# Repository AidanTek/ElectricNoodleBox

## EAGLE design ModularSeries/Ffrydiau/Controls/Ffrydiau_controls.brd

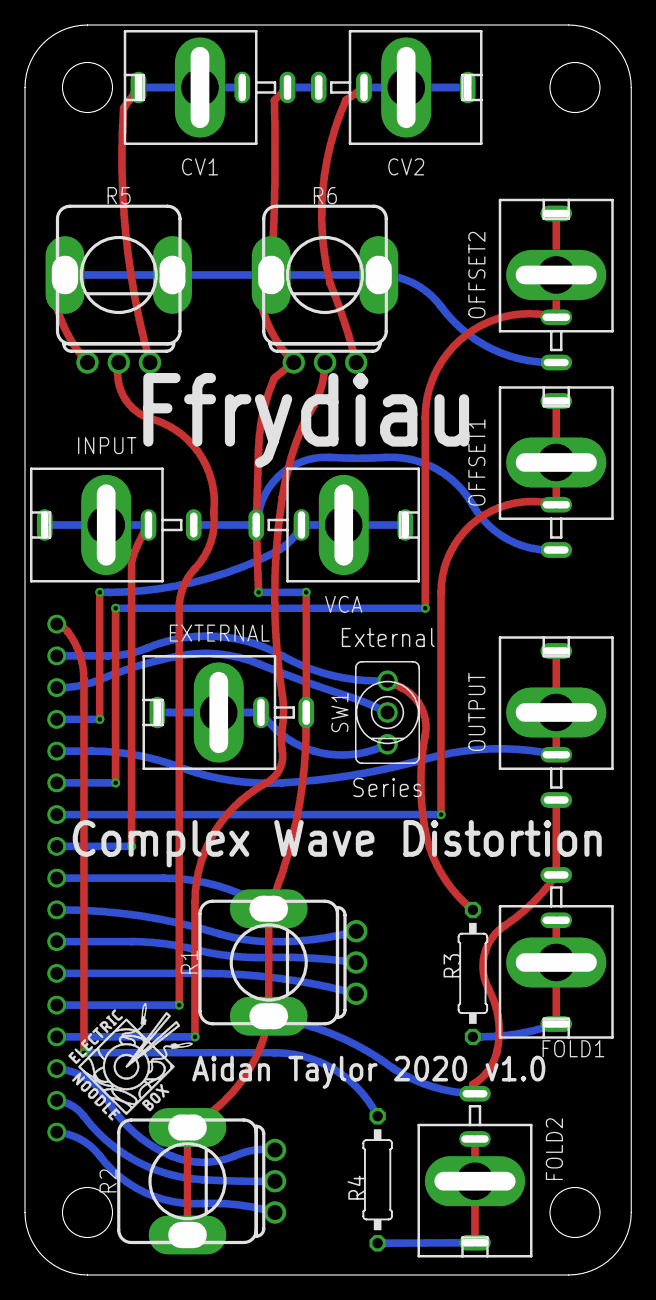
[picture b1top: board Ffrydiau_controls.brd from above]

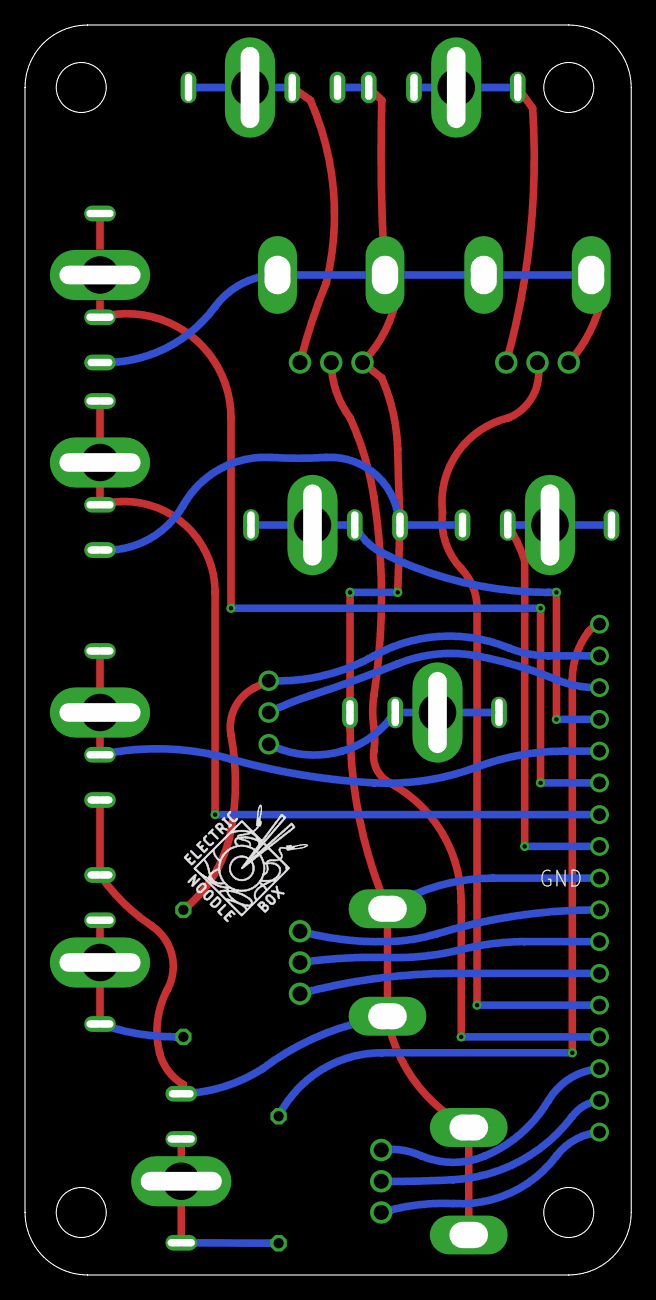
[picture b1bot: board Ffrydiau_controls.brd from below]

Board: 2 copper layers, 48.5 x 100.0 mm, 20 parts (2 on the bottom side), 22 nets.

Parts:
BOARD1: FFRYDIAU_LINK; FFRYDIAU
CV1, CV2: COMBI-JACKCINCHNANA; NEWCOMBOJACK_PANEL
EXTERNAL: COMBI-JACKCINCHNANA; NEWCOMBOJACK_PANEL
FOLD1, FOLD2: COMBI-JACKCINCHNANA; NEWCOMBOJACK_PANEL
INPUT: COMBI-JACKCINCHNANA; NEWCOMBOJACK_PANEL
OFFSET1, OFFSET2: COMBI-JACKCINCHNANA; NEWCOMBOJACK_PANEL
OUTPUT: COMBI-JACKCINCHNANA; NEWCOMBOJACK_PANEL
R1, R2, R5, R6: B100K; ALPHA_RV09_9MMPOT
R3, R4: 100Ω; 0207/10
SW1: SPDT_SWITCHDW1; MICRODPDT-DW1
U$1, U$2: LOGO10X10
VCA: COMBI-JACKCINCHNANA; NEWCOMBOJACK_PANEL

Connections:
AGND: BOARD1.GND, CV1.S, CV2.S, EXTERNAL.S, FOLD1.S, FOLD2.S, INPUT.S, OFFSET1.S, OFFSET2.S, OUTPUT.S, R1.LUGL, R1.LUGR, R2.LUGL, R2.LUGR, R5.C1, R5.LUGL, R5.LUGR, R6.C1, R6.LUGL, R6.LUGR, VCA.S
unnamed: CV1.CONN, CV1.T1, CV1.T2, R5.C3
unnamed: BOARD1.CV1, R5.C2
unnamed: BOARD1.SIG, INPUT.CONN, INPUT.T1, INPUT.T2
unnamed: BOARD1.OUT, OUTPUT.CONN, OUTPUT.T1, OUTPUT.T2
unnamed: BOARD1.POT1_2, R1.C2
unnamed: BOARD1.OFS1, OFFSET1.CONN, OFFSET1.T1, OFFSET1.T2
unnamed: BOARD1.OFS2, OFFSET2.CONN, OFFSET2.T1, OFFSET2.T2
unnamed: BOARD1.VCA, VCA.CONN, VCA.T1, VCA.T2
unnamed: BOARD1.POT1_1, R1.C1
unnamed: BOARD1.POT1_3, R1.C3
unnamed: BOARD1.POT2_2, R2.C2
unnamed: BOARD1.POT2_3, R2.C3
unnamed: BOARD1.POT2_1, R2.C1
unnamed: BOARD1.SWITCH_S, R3.1, SW1.C1
unnamed: FOLD1.CONN, FOLD1.T1, FOLD1.T2, R3.2
unnamed: BOARD1.SWITCH_R, SW1.C2
unnamed: EXTERNAL.CONN, EXTERNAL.T1, EXTERNAL.T2, SW1.C3
unnamed: BOARD1.FOLD2, R4.1
unnamed: FOLD2.CONN, FOLD2.T1, FOLD2.T2, R4.2
unnamed: CV2.CONN, CV2.T1, CV2.T2, R6.C3
unnamed: BOARD1.CV2, R6.C2

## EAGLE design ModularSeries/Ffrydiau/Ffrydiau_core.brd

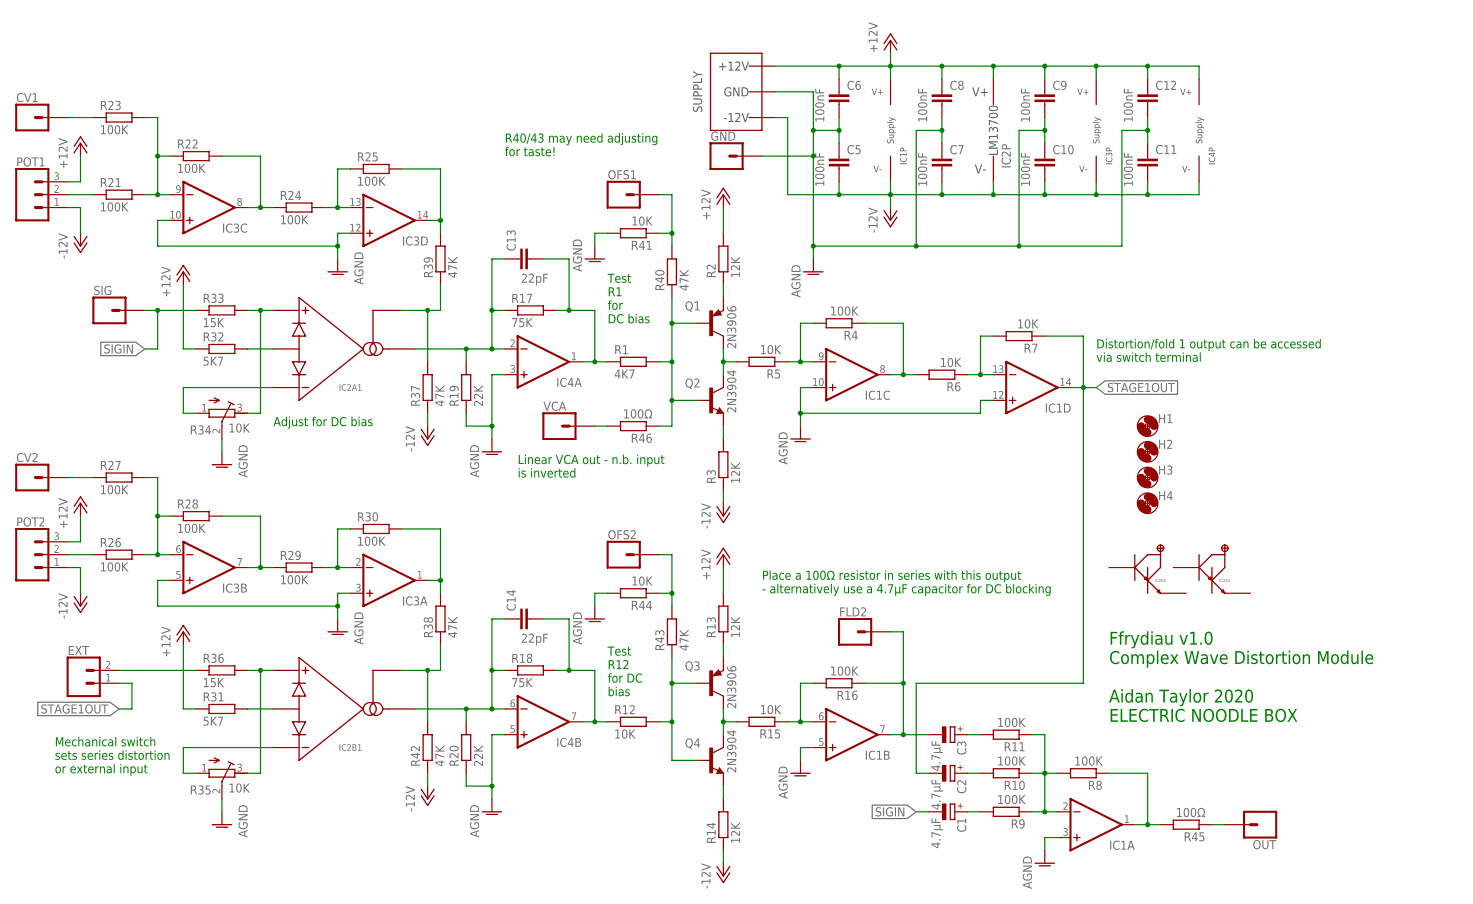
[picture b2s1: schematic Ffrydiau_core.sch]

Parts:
C1, C2, C3: 4.7µF; E2,5-6E
C5, C6, C7, C8, C9, C10, C11, C12: 100nF; C050-025X075
C13, C14: 22pF; C050-025X075
CV1, CV2: 1XWIREPAD; 1X01
EXT: 2XWIREPAD; 1X02
FLD2: 1XWIREPAD; 1X01
GND: 1XWIREPAD; 1X01
H1, H2, H3, H4: MOUNT-HOLE3.2; 3,2
IC1, IC3: TL0X4DIL; DIL14
IC2: LM13700DIL; DIL16
IC4: TL0X2DIL; DIL08
OFS1, OFS2: 1XWIREPAD; 1X01
OUT: 1XWIREPAD; 1X01
POT1, POT2: 3XWIREPAD; 1X03
Q1, Q3: 2N3906; TO92
Q2, Q4: 2N3904; TO92
R1: 4K7; 0207/10
R2, R3, R13, R14: 12K; 0207/10
R4, R8, R9, R10, R11, R16, R21, R22, R23, R24, R25, R26, R27, R28, R29, R30: 100K; 0207/10
R5, R6, R7, R12, R15, R41, R44: 10K; 0207/10
R17, R18: 75K; 0207/10
R19, R20: 22K; 0207/10
R31, R32: 5K7; 0207/10
R33, R36: 15K; 0207/10
R34, R35: 10K; RTRIM3296W
R37, R38, R39, R40, R42, R43: 47K; 0207/10
R45, R46: 100Ω; 0207/10
SIG: 1XWIREPAD; 1X01
VCA: 1XWIREPAD; 1X01
WP1: COMBO_SUPPLY_HEADER; COMBINED_POWER

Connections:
+12V: C6.1, C8.1, C9.1, C12.1, IC1.4 (V+), IC2.11 (V+), IC3.4 (V+), IC4.8 (V+), POT1.3, POT2.3, R2.2, R13.2, R31.1, R32.1, WP1.V+1 (V++), WP1.V+2 (V++), WP1.V+3 (V++)
-12V: C5.2, C7.2, C10.2, C11.2, IC1.11 (V-), IC2.6 (V-), IC3.11 (V-), IC4.4 (V-), POT1.1, POT2.1, R3.1, R14.1, R37.1, R42.1, WP1.V-1 (V--), WP1.V-2 (V--), WP1.V-3 (V--)
AGND: C5.1, C6.2, C7.1, C8.2, C9.2, C10.1, C11.1, C12.2, GND.1, IC1.3 (+IN), IC1.5 (+IN), IC1.10 (+IN), IC1.12 (+IN), IC3.3 (+IN), IC3.5 (+IN), IC3.10 (+IN), IC3.12 (+IN), IC4.3 (+IN), IC4.5 (+IN), R19.1, R20.1, R34.2 (S), R35.2 (S), R41.2, R44.2, WP1.GND1 (AGND), WP1.GND2 (AGND), WP1.GND3 (AGND), WP1.GND4 (AGND), WP1.GND5 (AGND), WP1.GND6 (AGND), WP1.GND7 (AGND), WP1.GND8 (AGND)
unnamed: Q1.2 (B), Q2.2 (B), R1.2, R40.1, R46.1
unnamed: Q1.3 (E), R2.1
unnamed: Q2.3 (E), R3.2
unnamed: Q1.1 (C), Q2.1 (C), R5.2
unnamed: IC1.9 (-IN), R4.2, R5.1
unnamed: IC1.8 (OUT), R4.1, R6.2
unnamed: IC1.13 (-IN), R6.1, R7.2
unnamed: OUT.1, R45.1
unnamed: C13.2, IC4.1 (OUT), R1.1, R17.2
unnamed: C3.+, R11.2
unnamed: C2.+, R10.2
unnamed: C1.+, R9.2
unnamed: IC1.2 (-IN), R8.2, R9.1, R10.1, R11.1
unnamed: IC1.1 (OUT), R8.1, R45.2
unnamed: Q3.2 (B), Q4.2 (B), R12.2, R43.1
unnamed: Q3.3 (E), R13.1
unnamed: Q4.3 (E), R14.2
unnamed: Q3.1 (C), Q4.1 (C), R15.2
unnamed: IC1.6 (-IN), R15.1, R16.2
unnamed: C3.-, FLD2.1, IC1.7 (OUT), R16.1
unnamed: C14.1, IC2.12 (AMPOUT), IC4.6 (-IN), R18.1, R20.2
unnamed: C13.1, IC2.5 (AMPOUT), IC4.2 (-IN), R17.1, R19.2
unnamed: C14.2, IC4.7 (OUT), R12.1, R18.2
unnamed: IC3.9 (-IN), R21.2, R22.1, R23.2
unnamed: IC3.8 (OUT), R22.2, R24.1
unnamed: IC3.13 (-IN), R24.2, R25.1
unnamed: IC3.14 (OUT), R25.2, R39.2
unnamed: CV2.1, R27.1
unnamed: IC3.1 (OUT), R30.2, R38.2
unnamed: POT1.2, R21.1
unnamed: IC3.2 (-IN), R29.2, R30.1
unnamed: CV1.1, R23.1
unnamed: IC3.7 (OUT), R28.2, R29.1
unnamed: IC3.6 (-IN), R26.2, R27.2, R28.1
unnamed: IC2.14 (AMP+), R35.3 (E), R36.2
unnamed: IC2.13 (AMP-), R35.1 (A)
unnamed: IC2.15 (DIODES), R31.2
unnamed: IC2.2 (DIODES), R32.2
unnamed: IC2.1 (AMPBIAS), R37.2, R39.1
unnamed: POT2.2, R26.1
unnamed: IC2.3 (AMP+), R33.2, R34.3 (E)
unnamed: IC2.4 (AMP-), R34.1 (A)
unnamed: IC2.16 (AMPBIAS), R38.1, R42.2
unnamed: OFS1.1, R40.2, R41.1
unnamed: OFS2.1, R43.2, R44.1
unnamed: R46.2, VCA.1
unnamed: EXT.2, R36.1
SIGIN: C1.-, R33.1, SIG.1
STAGE1OUT: C2.-, EXT.1, IC1.14 (OUT), R7.1

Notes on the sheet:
Place a 100Ω resistor in series with this output - alternatively use a 4.7µF capacitor for DC blocking
Distortion/fold 1 output can be accessed via switch terminal
R40/43 may need adjusting for taste!
Linear VCA out - n.b. input is inverted
Adjust for DC bias
Test R1 for DC bias
Test R12 for DC bias
Mechanical switch sets series distortion or external input
Ffrydiau v1.0 Complex Wave Distortion Module Aidan Taylor 2020 ELECTRIC NOODLE BOX

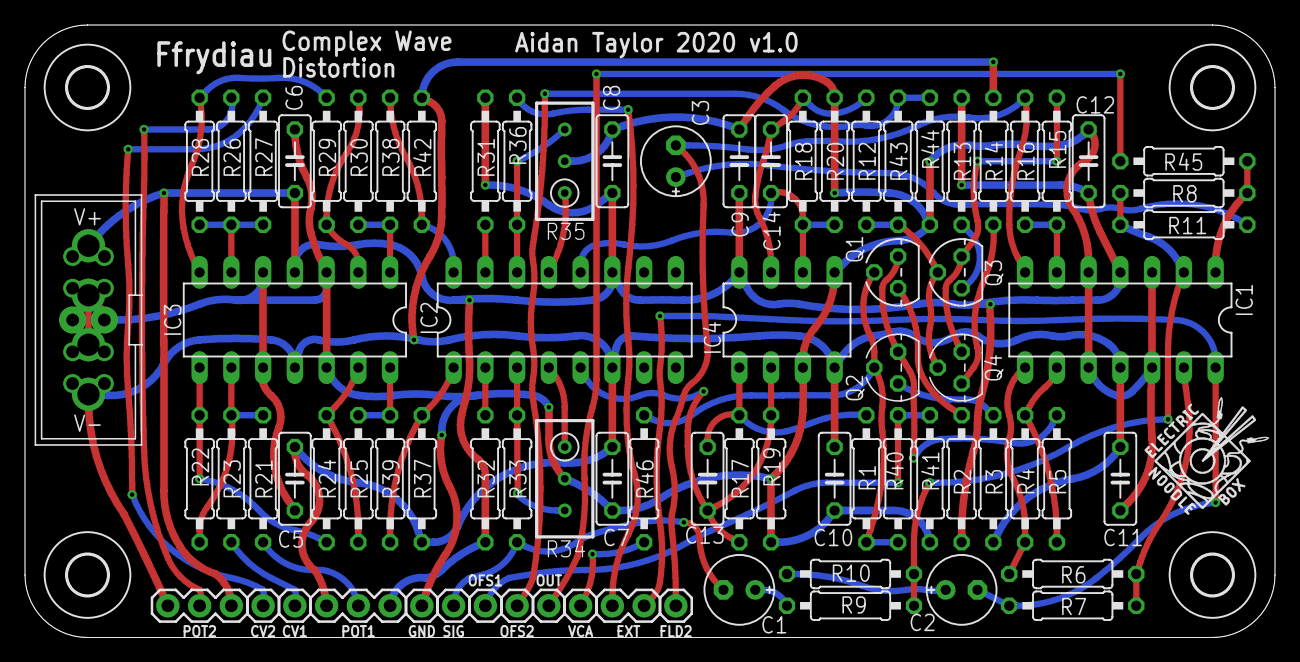
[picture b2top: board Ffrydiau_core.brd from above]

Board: 2 copper layers, 100.0 x 49.0 mm, 85 parts (0 on the bottom side), 52 nets.

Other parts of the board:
U$1: LOGO10X10

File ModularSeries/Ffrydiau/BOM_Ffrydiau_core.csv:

Qty,Value,Package,Parts,Description,RETAILER,CATALOGUE
,,,,,,
16,100K,0207/10,"R4, R8, R9, R10, R11, R16, R21, R22, R23, R24, R25, R26, R27, R28, R29, R30",RESISTOR 1/4W,Farnell,2329853
2,100Ω,0207/10,"R45, R46",RESISTOR 1/4W,Farnell,2329854
7,10K,0207/10,"R5, R6, R7, R12, R15, R41, R44",RESISTOR 1/4W,Farnell,2329855
4,12K,0207/10,"R2, R3, R13, R14",RESISTOR 1/4W,Farnell,2329863
2,15K,0207/10,"R33, R36",RESISTOR 1/4W,Farnell,1563095
2,22K,0207/10,"R19, R20",RESISTOR 1/4W,Farnell,2329901
6,47K,0207/10,"R37, R38, R39, R40, R42, R43",RESISTOR 1/4W,Farnell,2329944
1,4K7,0207/10,R1,RESISTOR 1/4W,Farnell,2329945
2,5K6,0207/10,"R31, R32",RESISTOR 1/4W,Farnell,2329958
2,75K,0207/10,"R17, R18",RESISTOR 1/4W,Farnell,2329972
2,10K,RTRIM3296W,"R34, R35",Trimm resistor 3296W,Farnell,9353186
,,,,,,
2,22pF,C050-025X075,"C13, C14",CAPACITOR Ceramic,Farnell,1457695
8,100nF,C050-025X075,"C5, C6, C7, C8, C9, C10, C11, C12",CAPACITOR Ceramic,Farnell,2797801
3,4.7¬µF,"E2,5-6E","C1, C2, C3","POLARIZED CAPACITOR, Electrolytic 25V+",Farnell,9451234
,,,,,,
2,2N3904,TO92,"Q2, Q4",NPN Transistor TO-92,Farnell,1574370
2,2N3906,TO92,"Q1, Q3",PNP Transistor TO-92,Farnell,1574372
1,LM13700,DIL16,IC2,Dual Transconductance Amplifier with Darlington Buffer,Farnell,3118206
1,TL082,DIL08,IC4,Dual Operational Amplifier,Farnell,1103189
2,TL084,DIL14,"IC1, IC3",Quad Operational Amplifier,Farnell,3005140
,,,,,,
1,Power Header,Power Header,WP1,10 way Shrouded IDC,Farnell,2843527
,,,,,,
9,Jack / Banana Connector,1X01,"CV1, CV2, FLD2, OFS1, OFS2, OUT, SIG, VCA",Banana or Jack patch point (panel part),Farnell,1698951
1,SPDT Mechanical Switch,1X02,EXT,Toggle switch SPDT (panel part),Farnell,9473491
2,B100K Potentiometer,1X03,"POT1, POT2",Taiwan Alpha 16mm (panel part),Rapid,65-0756

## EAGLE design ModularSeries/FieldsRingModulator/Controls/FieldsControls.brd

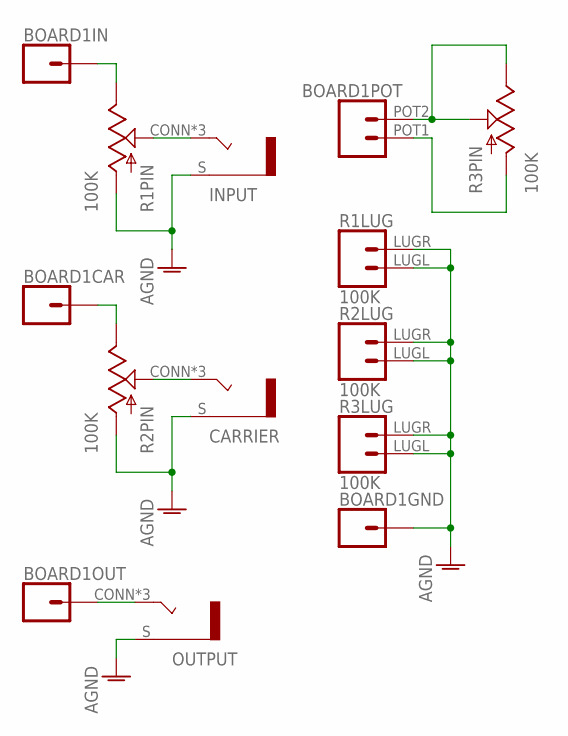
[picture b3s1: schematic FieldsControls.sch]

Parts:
BOARD1: FIELDS_LINK; FIELDS
CARRIER: COMBI-JACKCINCHNANA; NEWCOMBOJACK_PANEL
INPUT: COMBI-JACKCINCHNANA; NEWCOMBOJACK_PANEL
OUTPUT: COMBI-JACKCINCHNANA; NEWCOMBOJACK_PANEL
R1, R2, R3: 100K; ALPHA_RV09_9MMPOT

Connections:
AGND: BOARD1.GND (1), BOARD1.GND2 (1), CARRIER.S, INPUT.S, OUTPUT.S, R1.C1 (A), R1.LUGL (1), R1.LUGR (2), R2.C1 (A), R2.LUGL (1), R2.LUGR (2), R3.LUGL (1), R3.LUGR (2)
unnamed: BOARD1.IN (1), R1.C3 (B)
unnamed: INPUT.CONN (T), INPUT.T1 (T), INPUT.T2 (T), R1.C2 (W)
unnamed: BOARD1.OUT (1), OUTPUT.CONN (T), OUTPUT.T1 (T), OUTPUT.T2 (T)
unnamed: BOARD1.CAR (1), R2.C3 (B)
unnamed: CARRIER.CONN (T), CARRIER.T1 (T), CARRIER.T2 (T), R2.C2 (W)
unnamed: BOARD1.POT1 (1), R3.C1 (A)
unnamed: BOARD1.POT2 (2), R3.C2 (W), R3.C3 (B)

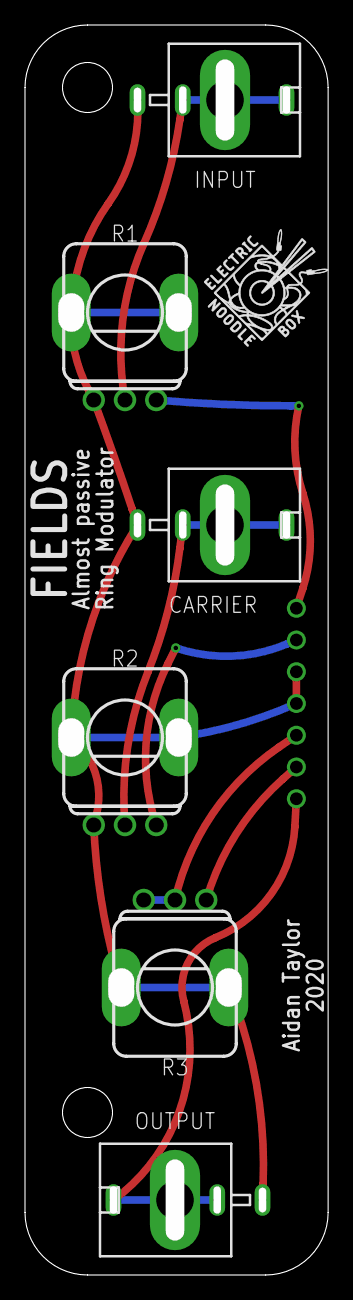
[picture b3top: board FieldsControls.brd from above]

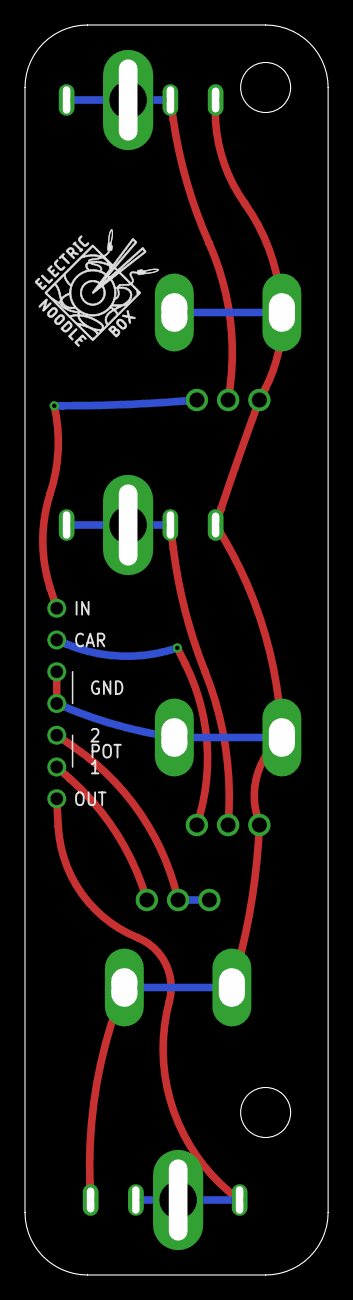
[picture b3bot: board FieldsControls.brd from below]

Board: 2 copper layers, 24.2 x 100.0 mm, 9 parts (2 on the bottom side), 8 nets.

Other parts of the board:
U$1, U$2: LOGO10X10

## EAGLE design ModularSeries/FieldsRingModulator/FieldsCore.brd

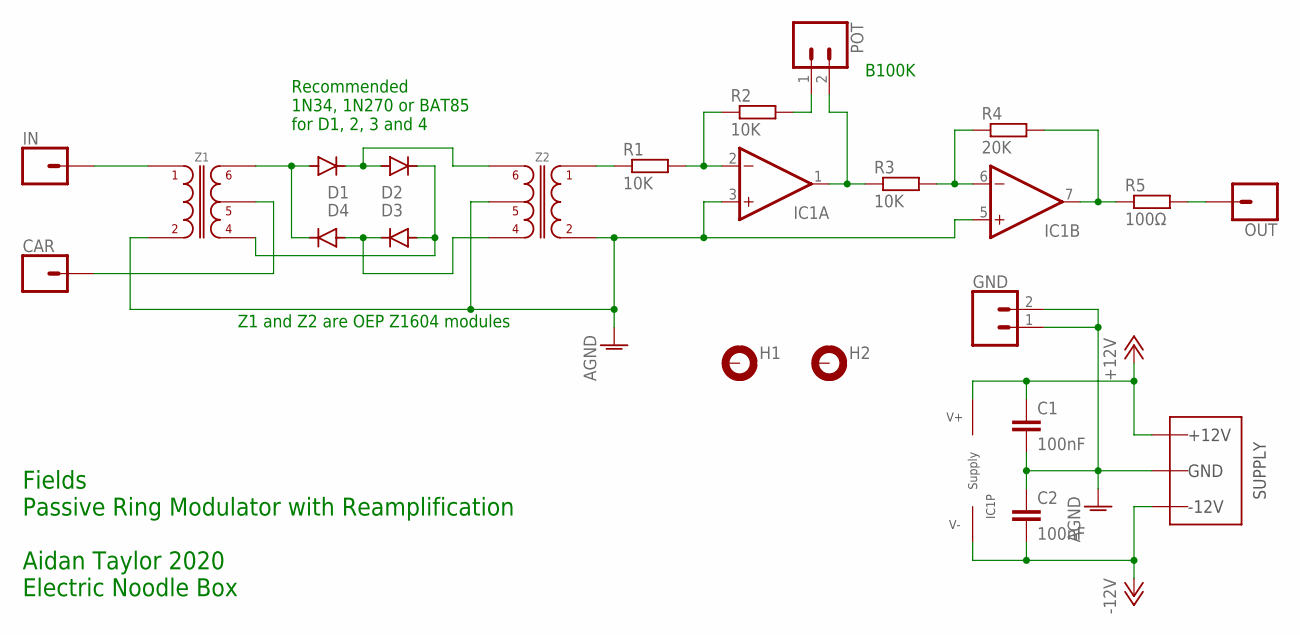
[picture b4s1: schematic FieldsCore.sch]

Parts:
C1, C2: 100nF; C050-025X075
CAR: 1XWIREPAD; 1X01
D1, D2, D3, D4: DIODE-DO35-10; DO35-10
GND: 2XWIREPAD; 1X02
H1, H2: MOUNT-PAD-ROUND3.2; 3,2-PAD
IC1: TL0X2DIL; DIL08
IN: 1XWIREPAD; 1X01
OUT: 1XWIREPAD; 1X01
POT: 2XWIREPAD; 1X02
R1, R2, R3: 10K; 0207/10
R4: 20K; 0207/10
R5: 100Ω; 0207/10
WP1: COMBO_SUPPLY_HEADER; COMBINED_POWER
Z1, Z2: Z1604_AUDIO_TRANSFORMER; Z1604_TRANSFORMER

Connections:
+12V: C1.1, IC1.8 (V+), WP1.V+1 (V++), WP1.V+2 (V++), WP1.V+3 (V++)
-12V: C2.2, IC1.4 (V-), WP1.V-1 (V--), WP1.V-2 (V--), WP1.V-3 (V--)
AGND: C1.2, C2.1, GND.1, GND.2, IC1.3 (+IN), IC1.5 (+IN), WP1.GND1 (AGND), WP1.GND2 (AGND), WP1.GND3 (AGND), WP1.GND4 (AGND), WP1.GND5 (AGND), WP1.GND6 (AGND), WP1.GND7 (AGND), WP1.GND8 (AGND), Z1.T3 (3), Z2.T3 (3), Z2.T5 (5)
unnamed: D1.A, D4.C, Z1.T6 (6)
unnamed: D1.C, D2.A, Z2.T6 (6)
unnamed: D2.C, D3.A, Z1.T4 (4)
unnamed: D3.C, D4.A, Z2.T4 (4)
unnamed: CAR.1, Z1.T5 (5)
unnamed: R1.1, Z2.T1 (1)
unnamed: IC1.2 (-IN), R1.2, R2.1
unnamed: IN.1, Z1.T1 (1)
unnamed: POT.1, R2.2
unnamed: IC1.1 (OUT), POT.2, R3.1
unnamed: IC1.6 (-IN), R3.2, R4.1
unnamed: IC1.7 (OUT), R4.2, R5.1
unnamed: OUT.1, R5.2

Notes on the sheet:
Recommended 1N34, 1N270 or BAT85 for D1, 2, 3 and 4
B100K
Z1 and Z2 are OEP Z1604 modules
Fields Passive Ring Modulator with Reamplification Aidan Taylor 2020 Electric Noodle Box

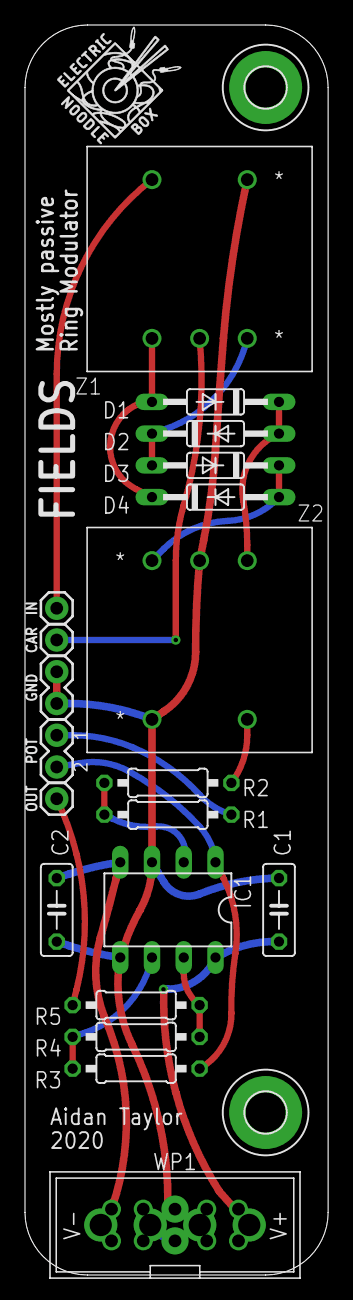
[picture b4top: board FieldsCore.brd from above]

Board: 2 copper layers, 24.2 x 100.0 mm, 24 parts (1 on the bottom side), 16 nets.

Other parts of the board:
U$1, U$2: LOGO10X10

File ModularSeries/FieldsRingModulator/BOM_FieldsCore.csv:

Qty,Value,Package,Parts,Description,Retailer,Catalogue
,,,,,,
1,100Ω,0207/10,R5,RESISTOR 1/4W,Farnell,2329854
3,10K,0207/10,"R1, R2, R3",RESISTOR 1/4W,Farnell,2329855
1,22K,0207/10,R4,RESISTOR 1/4W,Farnell,2329901
,,,,,,
2,100nF,C050-025X075,"C1, C2",CAPACITOR,Farnell,2797801
,,,,,,
4,"1n34, 1n270 or BAT85",DO35-10,"D1, D2, D3, D4",DIODE Germanium recommended,Farnell,1862942
1,NE5532,DIL08,IC1,Dual Operational Amplifier,Farnell,3117314
2,Z1604,Z1604_TRANSFORMER,"Z1, Z2",OEP Z1604,Farnell,1172421
,,,,,,
1,Power Header (Euro),,WP1,10 way Shrouded IDC,Farnell,2843527
1,Power Header (Alt),,WP1,4 way MTA156 (optional),Farnell,
,,,,,,
3,Banana Connector,,"CAR, IN, OUT",Banana or Jack Patch point,Farnell,1698951
1,B100K,,POT,Linear Potentiometer,Rapid,65-0753
